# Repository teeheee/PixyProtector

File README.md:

# Pixy Protector #

schützt die Pixy vor allen Hardware defekten.

### TODO ###

* make more pcbs

### Feedback, Fehler und Korrekturen ###

* email an alexander.ulbrich@uni-ulm.de

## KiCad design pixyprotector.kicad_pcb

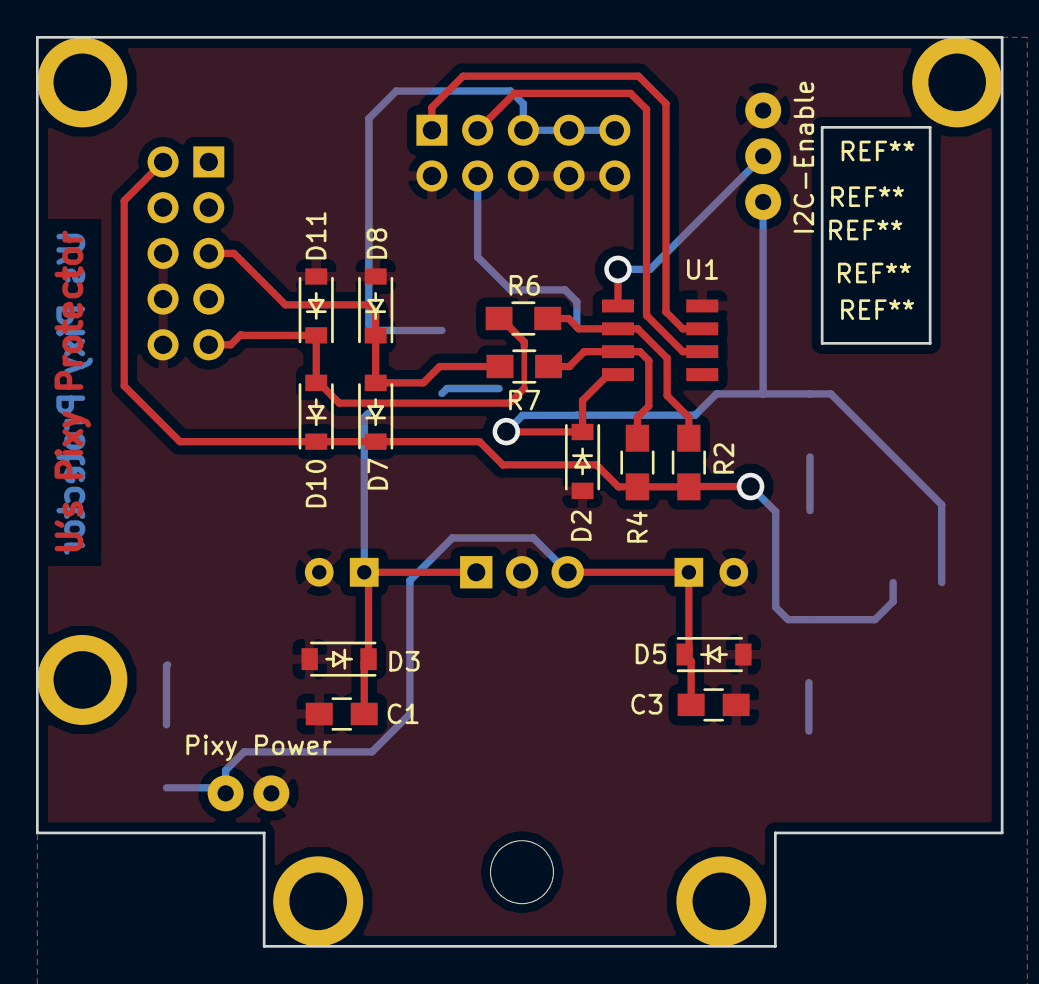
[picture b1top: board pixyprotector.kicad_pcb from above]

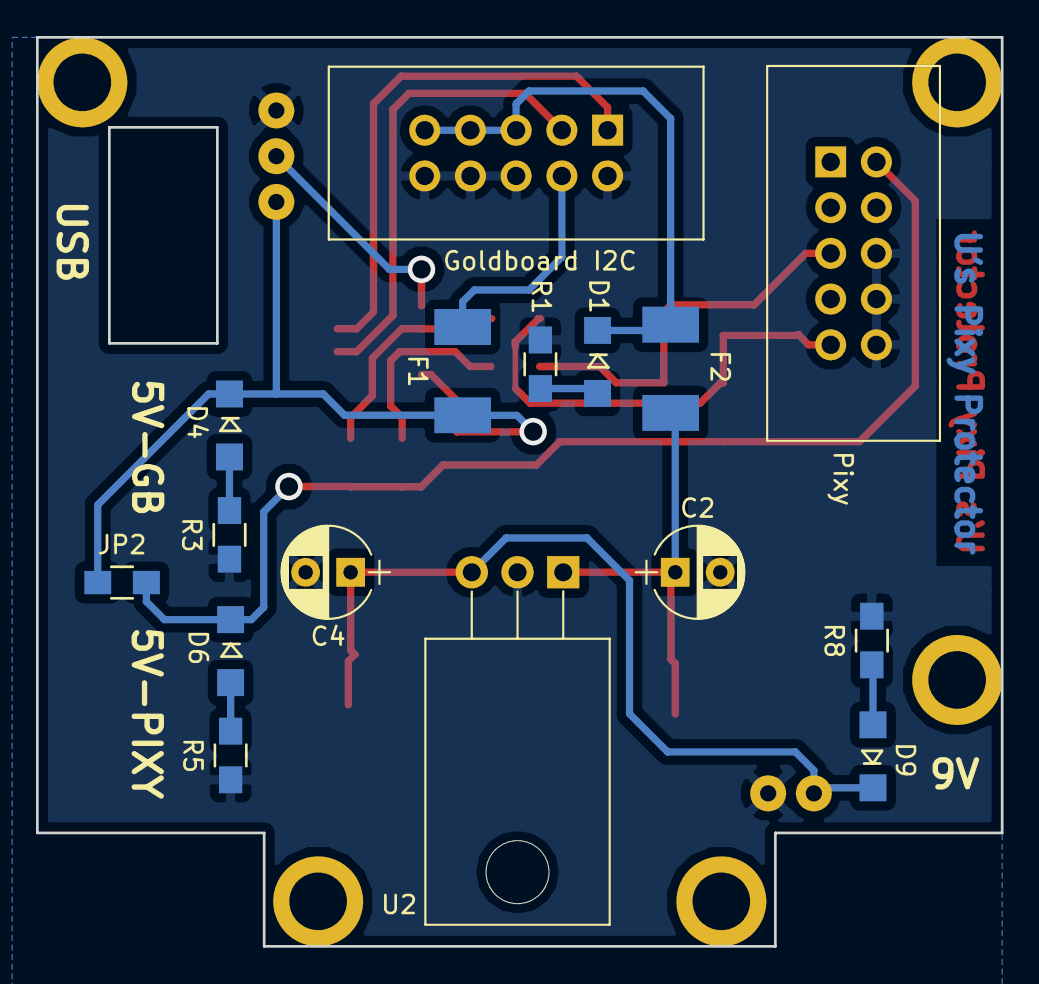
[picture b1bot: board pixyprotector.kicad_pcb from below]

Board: 2 copper layers, 53.6 x 50.5 mm, 32 parts (16 on the bottom side), 18 nets.

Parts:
C1, C3: 100n; C_0805
C2, C4: 47u; CP_Radial_D5.0mm_P2.50mm
D1, D4, D6, D9: LED; 1206_LED
D2, D3, D5, D7, D8, D10, D11: D_Schottky; Shotkey-SOD-123
F1, F2: Fuse; smd_fuse
Goldboard I2C: Goldboard I2C; Goldboard_I2C
I2C-Enable: Jumper_NC_Dual; 1x3_pinhead
JP2: Jumper; R_0805
Pixy: Pixy; PIXY
Pixy Power: pixy Power; 1x2_pinheader
R1, R8: 1k; R_0805
R2, R4: 4k7; R_0805
R3, R5: 470; R_0805
R6, R7: 200; R_0805
U1: PCA9515D; SO8
U2: 78S09; TO-220_Horizontal

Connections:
+5VA: D2.1, D4.2, F1.1, I2C-Enable.3, JP2.1, U1.8
+5VP: D6.2, D7.1, D10.1, JP2.2, Pixy.2, R2.1, R4.1
GND: C1.2, C2.2, C3.2, C4.2, D2.2, D3.2, D5.2, D8.2, D11.2, Goldboard I2C.2, Goldboard I2C.6, Goldboard I2C.8, Goldboard I2C.10, I2C-Enable.1, Pixy.6, Pixy.8, Pixy.10, Pixy Power.2, R1.2, R3.1, R5.1, R8.2, U1.4, U2.2
unnamed: C1.1, C2.1, D3.1, F2.1, U2.1
unnamed: C3.1, C4.1, D5.1, D9.2, Pixy Power.1, U2.3
unnamed: D1.1, R1.1
unnamed: D1.2, F2.2, Goldboard I2C.5, Goldboard I2C.7, Goldboard I2C.9
unnamed: D4.1, R3.2
unnamed: D6.1, R5.2
unnamed: D7.2, D8.1, Pixy.5, R7.1
unnamed: D9.1, R8.1
unnamed: D10.2, D11.1, Pixy.9, R6.1
unnamed: F1.2, Goldboard I2C.4
unnamed: Goldboard I2C.1, U1.3
unnamed: Goldboard I2C.3, U1.2
unnamed: I2C-Enable.2, U1.5
unnamed: R2.2, R6.2, U1.6
unnamed: R4.2, R7.2, U1.7
